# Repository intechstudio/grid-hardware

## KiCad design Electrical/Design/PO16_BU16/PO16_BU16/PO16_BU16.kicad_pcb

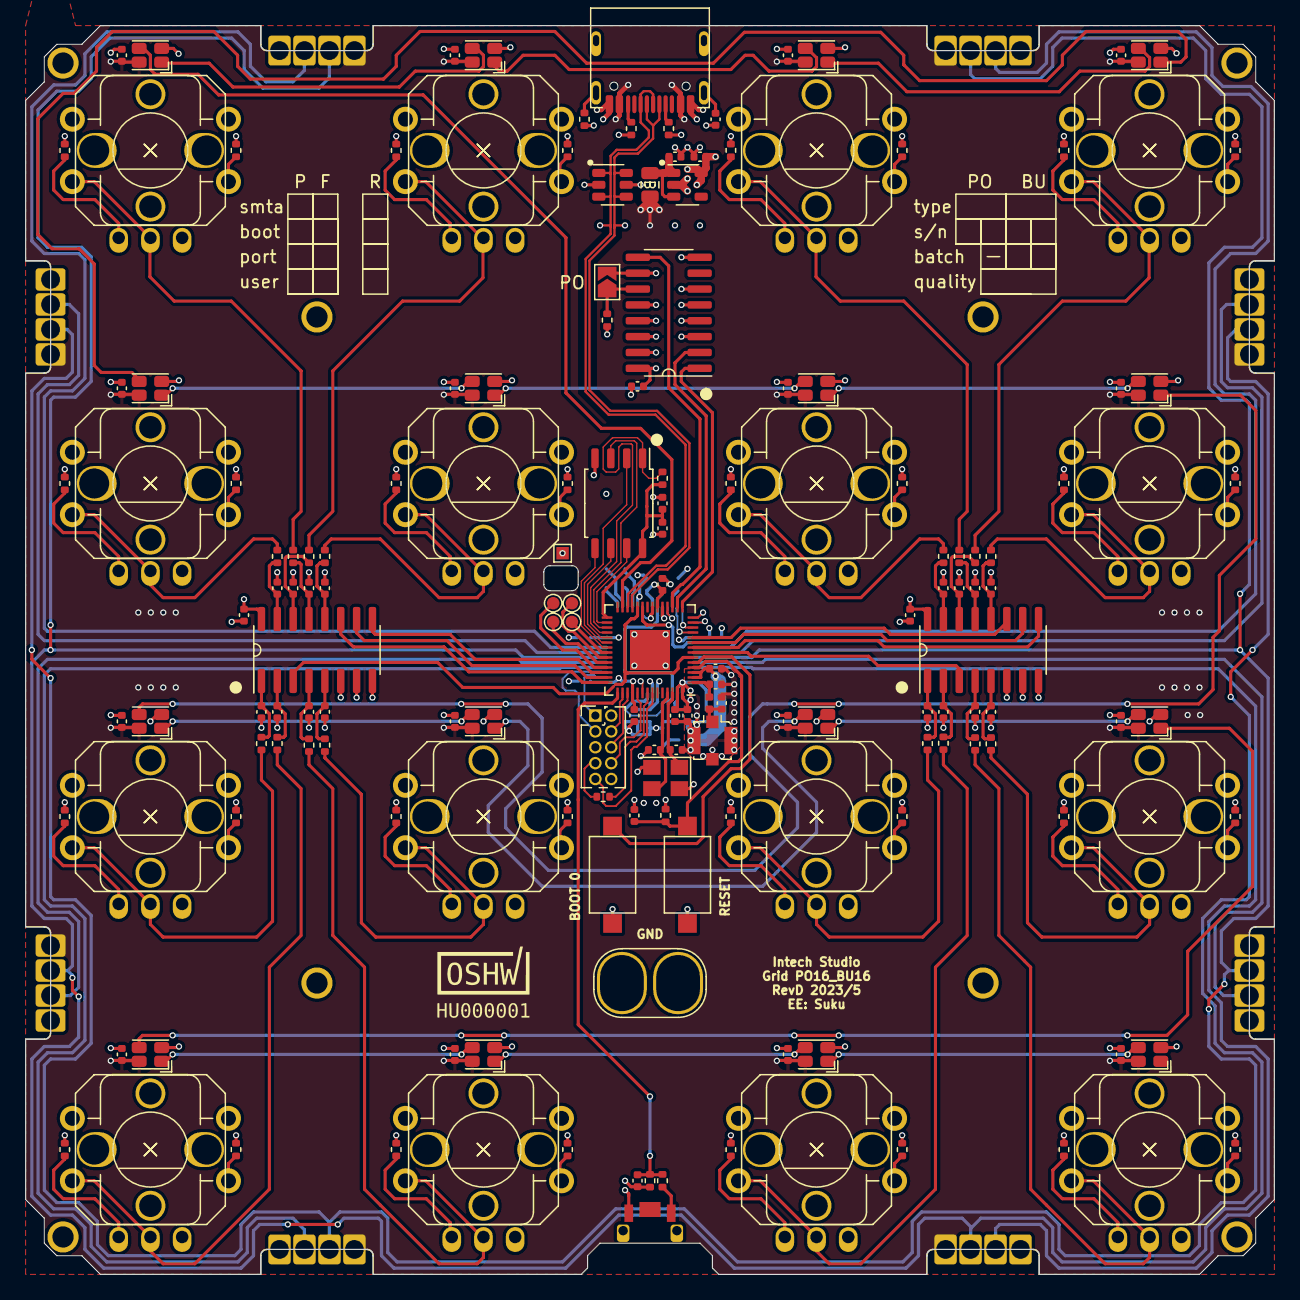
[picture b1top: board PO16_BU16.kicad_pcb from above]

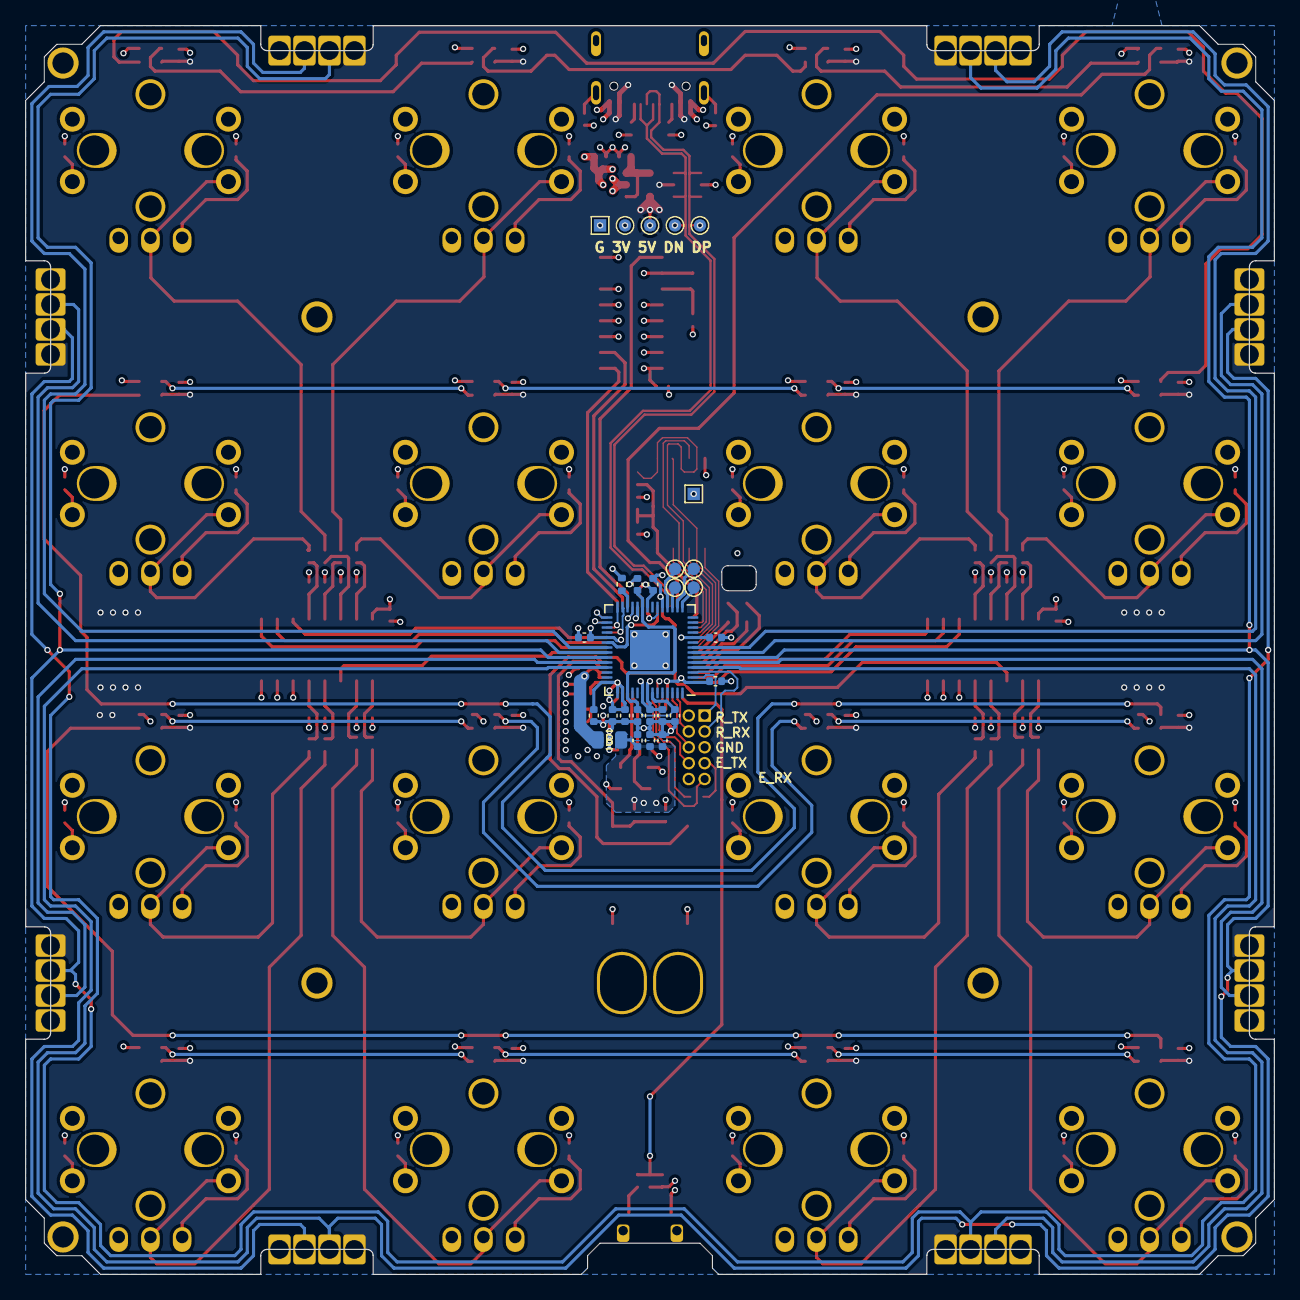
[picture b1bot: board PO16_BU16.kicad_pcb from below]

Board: 4 copper layers, 100.0 x 100.0 mm, 217 parts (28 on the bottom side), 155 nets.

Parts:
C731, C732, C735, C736, C737, C738, C740, C741, C744, C745, C747, C749, C751, C752, C756, C757, C801, C901, C902, C903, C904, C905, C906, C907, C908, C909, C910, C911, C912, C913, C914, C915, C916, C1001, C1002, C1003, C1004, C1005, C1006, C1007, C1008, C1009, C1010, C1011, C1012, C1013, C1014, C1015, C1016, C1017, C1018: 100n; CAP_0402
C733, C734, C746, C754, C755, C758, C760, C761: 1u; CAP_0402
C739: 3p9; CAP_0402
C742: 1p8; CAP_0402
C743: 10u; CAP_0402
C748, C750: 10p; CAP_0402
C753: 10n; CAP_0402
C759: 4n7; CAP_0402
D901, D902, D903, D904, D905, D906, D907, D908, D909, D910, D911, D912, D913, D914, D915, D916: WS2812C-2020; UI_WS2812C-2020
J701: Conn_Coaxial; U.FL_Molex_MCRF_73412-0110_Vertical
J702: (NF); PinHeader_2x05_P1.27mm_Vertical
J703, J704, J705, J706, J707, J708, J709, J710: AFB10-S08LCA-00; J_INTERFACE_SPRINGPATTERN
J711: USB_C_TYPE-C-32-M-12; USB_C_Korean_Hroparts_TYPE-C-31-M-12
J799: Conn_01x02; OscilloscopeGround
JP801: (NF); SolderJumper-2_P1.3mm_Open_TrianglePad1.0x1.5mm
L701: 1n8; IND_0402
L702, L703: GZ2012D601TF; FERRIT_0805
LOGO701: LOGO; OSHWA
M701: (NF); grid_outline
R701, R729, R734, R735, R738, R739, R801, R1033, R1034, R1035, R1036, R1037, R1038, R1039, R1040, R1041, R1042, R1043, R1044, R1045, R1046, R1047, R1048: 5k1; RES_0402
R733, R736, R1001, R1002, R1003, R1004, R1005, R1006, R1007, R1008, R1009, R1010, R1011, R1012, R1013, R1014, R1015, R1016: 1k; RES_0402
R737: 1M; RES_0402
R1017, R1018, R1019, R1020, R1021, R1022, R1023, R1024, R1025, R1026, R1027, R1028, R1029, R1030, R1031, R1032: 470R; RES_0402
SW701: C255807; SW_HYP_MAPMODE
SW702, SW703: C2905169; SW_SPST_CK_RS282G05A3
TP701, TP702, TP703, TP704, TP706, TP707, TP708, TP709: TestPoint; TestPoint_Pad_D1.0mm
TP705, TP710: TestPoint; TestPoint_Pad_1.0x1.0mm
TP711: GND; TestPoint_Pad_1.0x1.0mm
TP712: VB; TestPoint_Pad_D1.0mm
TP713: D-; TestPoint_Pad_D1.0mm
TP714: D+; TestPoint_Pad_D1.0mm
TP715: UI; TestPoint_Pad_D1.0mm
U703: RP2040; RP2040_QFN-56-1EP_7x7mm_P0.4mm_EP3.2x3.2mm
U704: ESP32-S3FN8; QFN-56-1EP_7x7mm_P0.4mm_EP3.2x3.2mm
U705: W25Q64JVSSIQ; SOIC-8W_FLASH
U706: SESRV05-4; SOT-23-6
U707: LN1134A332MR-G; SOT-23-5
U801: 74HC165; SOIC-16_74HC165
U1001, U1002: 74HC4051; SOIC-16_74HC4051
UI1001, UI1002, UI1003, UI1004, UI1005, UI1006, UI1007, UI1008, UI1009, UI1010, UI1011, UI1012, UI1013, UI1014, UI1015, UI1016: P090S-04F20BR10K (NF); UI_POT_TT
UI1017, UI1018, UI1019, UI1020, UI1021, UI1022, UI1023, UI1024, UI1025, UI1026, UI1027, UI1028, UI1029, UI1030, UI1031, UI1032: B3F-4050 (NF); UI_BUTTON_OMRON
Y701: ESP32_XTAL; Crystal_SMD_Abracon_ABM8G-4Pin_3.2x2.5mm

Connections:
+1V1: C731.1, C732.1, C733.1, U703.23 (DVDD), U703.45 (VREG_VOUT), U703.50 (DVDD)
+3V3: C734.1, C735.1, C736.1, C737.1, C738.1, C740.1, C741.1, C743.1, C744.1, C745.1, C746.1, C747.1, C751.1, C752.1, C753.1, C754.1, C757.2, C761.2, C801.1, C1009.1, C1018.1, L702.2, R701.1, R729.1, R735.1, R801.1, R1017.1, R1018.1, R1019.1, R1020.1, R1021.1, R1022.1, R1023.1, R1024.1, R1025.1, R1026.1, R1027.1, R1028.1, R1029.1, R1030.1, R1031.1, R1032.1, R1033.2, R1034.2, R1035.2, R1036.2, R1037.2, R1038.2, R1039.2, R1040.2, R1041.2, R1042.2, R1043.2, R1044.2, R1045.2, R1046.2, R1047.2, R1048.2, TP715.1, U703.1 (IOVDD), U703.10 (IOVDD), U703.22 (IOVDD), U703.33 (IOVDD), U703.42 (IOVDD), U703.43 (ADC_AVDD), U703.44 (VREG_IN), U703.48 (USB_VDD), U703.49 (IOVDD), U704.20 (VDD3P3_RTC), U704.46 (VDD3P3_CPU), U704.55 (VDDA1), U704.56 (VDDA2), U707.5 (OUT), U801.6 (D7), U801.16 (VCC), U1001.16 (VDD), U1002.16 (VDD)
+5V: C901.2, C902.2, C903.2, C904.2, C905.2, C906.2, C907.2, C908.2, C909.2, C910.2, C911.2, C912.2, C913.2, C914.2, C915.2, C916.2, D901.4 (VDD), D902.4 (VDD), D903.4 (VDD), D904.4 (VDD), D905.4 (VDD), D906.4 (VDD), D907.4 (VDD), D908.4 (VDD), D909.4 (VDD), D910.4 (VDD), D911.4 (VDD), D912.4 (VDD), D913.4 (VDD), D914.4 (VDD), D915.4 (VDD), D916.4 (VDD), J703.4, J704.1, J705.1, J706.4, J707.4, J708.1, J709.1, J710.4, J711.A4B9 (VBUS), J711.A9B4 (VBUS), L703.2, TP712.1, U706.5
/ANA_0: R1001.2, UI1001.2, UI1017.3
/ANA_1: R1005.2, UI1005.2, UI1021.3
/ANA_2: R1009.2, UI1009.2, UI1025.3
/ANA_3: R1013.2, UI1013.2, UI1029.3
/ANA_4: R1002.2, UI1002.2, UI1018.3
/ANA_5: R1006.2, UI1006.2, UI1022.3
/ANA_6: R1010.2, UI1010.2, UI1026.3
/ANA_7: R1014.2, UI1014.2, UI1030.3
/ANA_8: R1003.2, UI1003.2, UI1019.3
/ANA_9: R1007.2, UI1007.2, UI1023.3
/ANA_10: R1011.2, UI1011.2, UI1027.3
/ANA_11: R1015.2, UI1015.2, UI1031.3
/ANA_12: R1004.2, UI1004.2, UI1020.3
/ANA_13: R1008.2, UI1008.2, UI1024.3
/ANA_14: R1012.2, UI1012.2, UI1028.3
/ANA_15: R1016.2, UI1016.2, UI1032.3
/HWCFG/HWCFG_CLOCK: U704.16 (GPIO11), U801.2 (CLK)
/HWCFG/HWCFG_DATA: U704.17 (GPIO12), U801.9 (Q)
/HWCFG/HWCFG_SHIFT: U704.15 (GPIO10), U801.1 (SH/~LD)
/MCU/ESP_BOOT0: SW703.2 (B), U704.5 (GPIO0)
/MCU/ESP_LNA: C742.1, L701.2, U704.1 (LNA_IN)
/MCU/ESP_RESET: C758.1, R735.2, SW702.2 (B), U704.4 (CHIP_PU)
/MCU/GRID_EAST_RX: J709.3, U703.36 (GPIO24)
/MCU/GRID_EAST_TX: J710.2, U703.38 (GPIO26_ADC0)
/MCU/GRID_NORTH_RX: J705.3, U703.8 (GPIO6)
/MCU/GRID_NORTH_TX: J707.2, U703.35 (GPIO23)
/MCU/GRID_SOUTH_RX: J708.3, U703.39 (GPIO27_ADC1)
/MCU/GRID_SOUTH_TX: J706.2, U703.4 (GPIO2)
/MCU/GRID_SYNC_1: J703.3, J706.3, J707.3, J710.3, U703.37 (GPIO25)
/MCU/GRID_SYNC_2: J704.2, J705.2, J708.2, J709.2, U703.6 (GPIO4)
/MCU/GRID_WEST_RX: J704.3, U703.5 (GPIO3)
/MCU/GRID_WEST_TX: J703.2, U703.7 (GPIO5)
/MCU/LED_DATA_OUT: D901.3 (DIN), U704.27 (GPIO21)
/MCU/MAP_MODE: C757.1, R701.2, R736.2, U704.43 (GPIO38)
/MCU/RP_CLK: U703.20 (XIN), U704.21 (GPIO15)
/MCU/RP_INTERRUPT: U703.34 (GPIO22), U704.23 (GPIO17)
/MCU/RP_RUN: R729.2, U703.26 (RUN)
/MCU/RP_SPI0_CS: U703.28 (GPIO17), U704.12 (GPIO7)
/MCU/RP_SPI0_RX: U703.27 (GPIO16), U704.11 (GPIO6)
/MCU/RP_SPI0_SCK: U703.29 (GPIO18), U704.14 (GPIO9)
/MCU/RP_SPI0_TX: U703.30 (GPIO19), U704.13 (GPIO8)
/MCU/RP_SWCLK: U703.24 (SWCLK), U704.19 (GPIO14)
/MCU/RP_SWDIO: U703.25 (SWD), U704.18 (GPIO13)
/MCU/RP_UART0_RX: J702.3, U703.3 (GPIO1)
/MCU/RP_UART0_TX: J702.1, U703.2 (GPIO0)
/MCU/SPICLK: U704.33 (GPIO30), U705.6 (CLK)
/MCU/SPICS0: R734.2, U704.32 (GPIO29), U705.1 (~CS)
/MCU/SPID: U704.35 (GPIO32), U705.5 (DI(IO0))
/MCU/SPIHD: U704.30 (GPIO27), U705.7 (IO3)
/MCU/SPIQ: U704.34 (GPIO31), U705.2 (DO(IO1))
/MCU/SPIWP: U704.31 (GPIO28), U705.3 (IO2)
/MCU/TCK: J702.4, U704.44 (GPIO39)
/MCU/TDI: J702.8, U704.47 (GPIO41)
/MCU/TDO: J702.6, U704.45 (GPIO40)
/MCU/TMS: J702.2, U704.48 (GPIO42)
/MCU/U0RXD: J702.9, U704.50 (GPIO44)
/MCU/U0TXD: R733.2, U704.49 (GPIO43)
/MCU/USB_DN: J711.A7 (D-), J711.B7 (D-), TP713.1, U704.25 (GPIO19), U706.4, U706.6
/MCU/USB_DP: J711.A6 (D+), J711.B6 (D+), TP714.1, U704.26 (GPIO20), U706.1, U706.3
ESP_GPIO_1: U704.6 (GPIO1), U704.24 (GPIO18), U1001.3 (X)
ESP_GPIO_2: U704.7 (GPIO2), U1002.3 (X)
ESP_GPIO_3: U704.8 (GPIO3), U1002.9 (C)
ESP_GPIO_4: U704.9 (GPIO4), U1002.10 (B)
ESP_GPIO_5: U704.10 (GPIO5), U1002.11 (A)
ESP_GPIO_33: TP709.1, U704.38 (GPIO33)
ESP_GPIO_34: TP708.1, U704.39 (GPIO34)
ESP_GPIO_35: U704.40 (GPIO35), U1001.9 (C)
ESP_GPIO_36: U704.41 (GPIO36), U1001.10 (B)
ESP_GPIO_37: U704.42 (GPIO37), U1001.11 (A)
ESP_GPIO_47: TP706.1, U704.37 (GPIO47)
ESP_GPIO_48: TP707.1, U704.36 (GPIO48)
GND: C731.2, C732.2, C733.2, C734.2, C735.2, C736.2, C737.2, C738.2, C739.2, C740.2, C741.2, C742.2, C743.2, C744.2, C745.2, C746.2, C747.2, C748.2, C749.2, C750.2, C751.2, C752.2, C753.2, C754.2, C755.2, C756.2, C758.2, C759.2, C760.2, C761.1, C801.2, C901.1, C902.1, C903.1, C904.1, C905.1, C906.1, C907.1, C908.1, C909.1, C910.1, C911.1, C912.1, C913.1, C914.1, C915.1, C916.1, C1001.2, C1002.2, C1003.2, C1004.2, C1005.2, C1006.2, C1007.2, C1008.2, C1009.2, C1010.2, C1011.2, C1012.2, C1013.2, C1014.2, C1015.2, C1016.2, C1017.2, C1018.2, D901.2 (VSS), D902.2 (VSS), D903.2 (VSS), D904.2 (VSS), D905.2 (VSS), D906.2 (VSS), D907.2 (VSS), D908.2 (VSS), D909.2 (VSS), D910.2 (VSS), D911.2 (VSS), D912.2 (VSS), D913.2 (VSS), D914.2 (VSS), D915.2 (VSS), D916.2 (VSS), J701.2 (Ext), J702.5, J703.1, J704.4, J705.4, J706.1, J707.1, J708.4, J709.4, J710.1, J711.A1B12 (GND), J711.A12B1 (GND), J799.1, J799.2, JP801.2 (B), R737.2, R738.2, R739.2, SW701.2 (B), SW702.1 (A), SW703.1 (A), TP705.1, TP710.1, TP711.1, U703.19 (TESTEN), U703.57 (GND), U704.57 (GND), U705.4 (GND), U706.2, U707.2 (GND), U801.3 (D4), U801.4 (D5), U801.5 (D6), U801.8 (GND), U801.10 (SI), U801.12 (D1), U801.13 (D2), U801.14 (D3), U801.15 (INH), U1001.6 (Inh), U1001.7 (VEE), U1001.8 (VSS), U1002.6 (Inh), U1002.7 (VEE), U1002.8 (VSS), UI1001.3, UI1002.3, UI1003.3, UI1004.3, UI1005.3, UI1006.3, UI1007.3, UI1008.3, UI1009.3, UI1010.3, UI1011.3, UI1012.3, UI1013.3, UI1014.3, UI1015.3, UI1016.3, UI1017.1, UI1017.2, UI1018.1, UI1018.2, UI1019.1, UI1019.2, UI1020.1, UI1020.2, UI1021.1, UI1021.2, UI1022.1, UI1022.2, UI1023.1, UI1023.2, UI1024.1, UI1024.2, UI1025.1, UI1025.2, UI1026.1, UI1026.2, UI1027.1, UI1027.2, UI1028.1, UI1028.2, UI1029.1, UI1029.2, UI1030.1, UI1030.2, UI1031.1, UI1031.2, UI1032.1, UI1032.2, Y701.2, Y701.4
unnamed: C749.1, L702.1, U704.2 (VDD3P3), U704.3 (VDD3P3)
unnamed: C760.1, L703.1, U707.1 (IN), U707.3 (EN)
unnamed: C759.1, J711.S1 (SHIELD)
unnamed: D901.1 (DOUT), D905.3 (DIN)
unnamed: D902.3 (DIN), D913.1 (DOUT)
unnamed: D902.1 (DOUT), D906.3 (DIN)
unnamed: D903.3 (DIN), D914.1 (DOUT)
unnamed: D903.1 (DOUT), D907.3 (DIN)
unnamed: D904.3 (DIN), D915.1 (DOUT)
unnamed: D904.1 (DOUT), D908.3 (DIN)
unnamed: D905.1 (DOUT), D909.3 (DIN)
unnamed: D906.1 (DOUT), D910.3 (DIN)
unnamed: D907.1 (DOUT), D911.3 (DIN)
unnamed: D908.1 (DOUT), D912.3 (DIN)
unnamed: D909.1 (DOUT), D913.3 (DIN)
unnamed: D910.1 (DOUT), D914.3 (DIN)
unnamed: D911.1 (DOUT), D915.3 (DIN)
unnamed: D912.1 (DOUT), D916.3 (DIN)
unnamed: C739.1, J701.1 (In), L701.1
unnamed: J702.7, R733.1
unnamed: J711.A5 (CC1), R738.1
unnamed: J711.B5 (CC2), R739.1
unnamed: J711.S2 (SHIELD), R737.1
unnamed: JP801.1 (A), R801.2, U801.11 (D0)
unnamed: R1017.2, UI1001.1
unnamed: R1018.2, UI1002.1
unnamed: R1019.2, UI1003.1
unnamed: R1020.2, UI1004.1
unnamed: R1021.2, UI1005.1
unnamed: R1022.2, UI1006.1
unnamed: R1023.2, UI1007.1
unnamed: R1024.2, UI1008.1
unnamed: R1025.2, UI1009.1
unnamed: R1026.2, UI1010.1
unnamed: R1027.2, UI1011.1
unnamed: R1028.2, UI1012.1
unnamed: R1029.2, UI1013.1
unnamed: R1030.2, UI1014.1
unnamed: R1031.2, UI1015.1
unnamed: R1032.2, UI1016.1
unnamed: R1033.1, UI1017.4
unnamed: R1034.1, UI1018.4
unnamed: R1035.1, UI1019.4
unnamed: R1036.1, UI1020.4
unnamed: R1037.1, UI1021.4
unnamed: R1038.1, UI1022.4
unnamed: R1039.1, UI1023.4
unnamed: R1040.1, UI1024.4
unnamed: R1041.1, UI1025.4
unnamed: R1042.1, UI1026.4
unnamed: R1043.1, UI1027.4
unnamed: R1044.1, UI1028.4
unnamed: R1045.1, UI1029.4
unnamed: R1046.1, UI1030.4
unnamed: R1047.1, UI1031.4
unnamed: R1048.1, UI1032.4
unnamed: R736.1, SW701.1 (A)
unnamed: TP701.1, U703.15 (GPIO12)
unnamed: TP702.1, U703.16 (GPIO13)
unnamed: TP703.1, U703.17 (GPIO14)
unnamed: TP704.1, U703.18 (GPIO15)
unnamed: C750.1, U704.53 (XTAL_N), Y701.3
unnamed: C748.1, U704.54 (XTAL_P), Y701.1
unnamed: C1001.1, R1001.1, U1001.13 (X0)
unnamed: C1005.1, R1005.1, U1001.14 (X1)
unnamed: C1002.1, R1002.1, U1001.15 (X2)
unnamed: C1006.1, R1006.1, U1001.12 (X3)
unnamed: C1003.1, R1003.1, U1001.1 (X4)
unnamed: C1007.1, R1007.1, U1001.5 (X5)
unnamed: C1004.1, R1004.1, U1001.2 (X6)
unnamed: C1008.1, R1008.1, U1001.4 (X7)
unnamed: C1010.1, R1009.1, U1002.13 (X0)
unnamed: C1014.1, R1013.1, U1002.14 (X1)
unnamed: C1011.1, R1010.1, U1002.15 (X2)
unnamed: C1015.1, R1014.1, U1002.12 (X3)
unnamed: C1012.1, R1011.1, U1002.1 (X4)
unnamed: C1016.1, R1015.1, U1002.5 (X5)
unnamed: C1013.1, R1012.1, U1002.2 (X6)
unnamed: C1017.1, R1016.1, U1002.4 (X7)
VDD_SPI: C755.1, C756.1, R734.1, U704.29 (VDD_SPI), U705.8 (VCC)

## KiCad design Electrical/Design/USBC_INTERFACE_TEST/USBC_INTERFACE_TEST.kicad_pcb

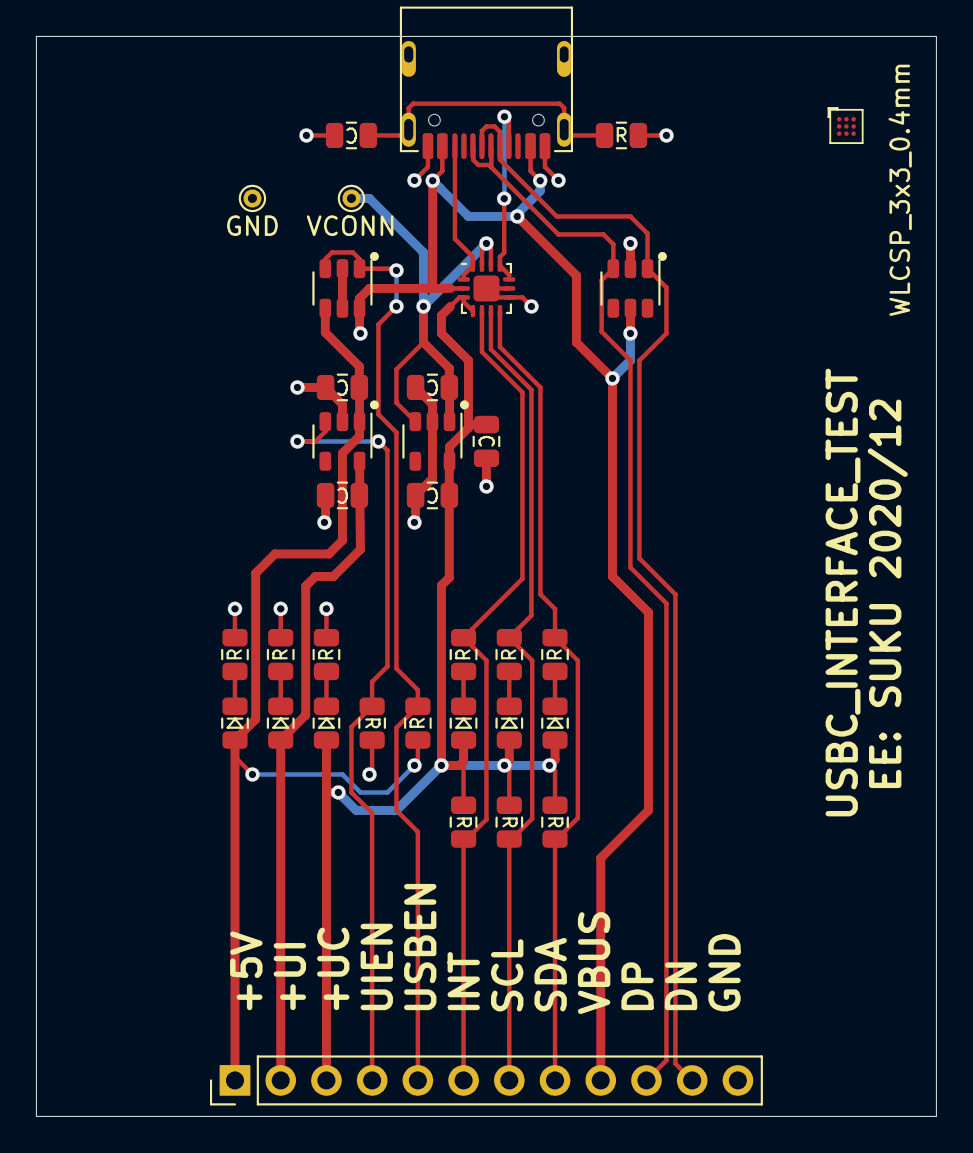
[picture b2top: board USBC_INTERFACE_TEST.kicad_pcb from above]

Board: 2 copper layers, 50.0 x 60.0 mm, 33 parts (0 on the bottom side), 23 nets.

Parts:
C1: 100n; CAP_0805
C2, C3, C4, C5: 1u; CAP_0805
C6: 4n7; CAP_0805
D1, D2, D3, D4, D5, D6: LED; LED_0805
J1: USB_C_TYPE-C-32-M-12; USB_C_Korean_Hroparts_TYPE-C-31-M-12
J2: Conn_01x12; PinHeader_1x12_P2.54mm_Vertical
Q1: WST2011; SOT-23-6
R1: 1M; RES_0805
R2, R4, R5: 2k2; RES_0805
R3, R6, R12: 10k; RES_0805
R7, R8, R9, R10, R11: 5k1; RES_0805
TP1: GND; TestPoint_THTPad_D1.0mm_Drill0.5mm
TP2: VCONN; TestPoint_THTPad_D1.0mm_Drill0.5mm
U1: FUSB302BMPX; WQFN-14-1EP_2.5x2.5mm_P0.5mm_EP1.45x1.45mm
U2, U3: U_REGULATOR_SOT23-5; SOT-23-5
U4: U_ESD_4ch; SOT-23-6

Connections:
+3V3_UC: C1.1, C2.1, D3.2, D4.2, D5.2, D6.2, J2.3, R2.1, R4.1, R5.1, U1.3, U1.4, U3.5
+3V3_UI: C5.1, D2.2, J2.2, U2.5
+5V: C3.1, D1.2, J2.1, Q1.4, R12.1, U2.1
/CC1: J1.A5, U1.10, U1.11
/CC2: J1.B5, U1.1, U1.14
/UI_PWR_EN: J2.4, R3.1, U2.3
/USB_DN: J1.A7, J1.B7, J2.11, U4.1
/USB_DP: J1.A6, J1.B6, J2.10, U4.3
/USB_INT: J2.6, R5.2, R9.2, U1.5
/USB_PWR_EN: J2.5, Q1.1, Q1.3, R12.2
/USB_SCL: J2.7, R4.2, R10.2, U1.6
/USB_SDA: J2.8, R2.2, R11.2, U1.7
/VCONN: C4.1, TP2.1, U1.12, U1.13, U3.1, U3.3
GND: C1.2, C2.2, C3.2, C4.2, C5.2, C6.2, J1.A1B12, J1.A12B1, J2.12, R1.2, R3.2, R6.2, R7.2, R8.2, TP1.1, U1.8, U1.9, U1.15, U2.2, U3.2, U4.2
unnamed: C6.1, J1.S1, J1.S2, R1.1
unnamed: D1.1, R6.1
unnamed: D2.1, R7.1
unnamed: D3.1, R8.1
unnamed: D4.1, R9.1
unnamed: D5.1, R10.1
unnamed: D6.1, R11.1
unnamed: Q1.2, Q1.5
VBUS: J1.A4B9, J1.A9B4, J2.9, Q1.6, U1.2, U4.5

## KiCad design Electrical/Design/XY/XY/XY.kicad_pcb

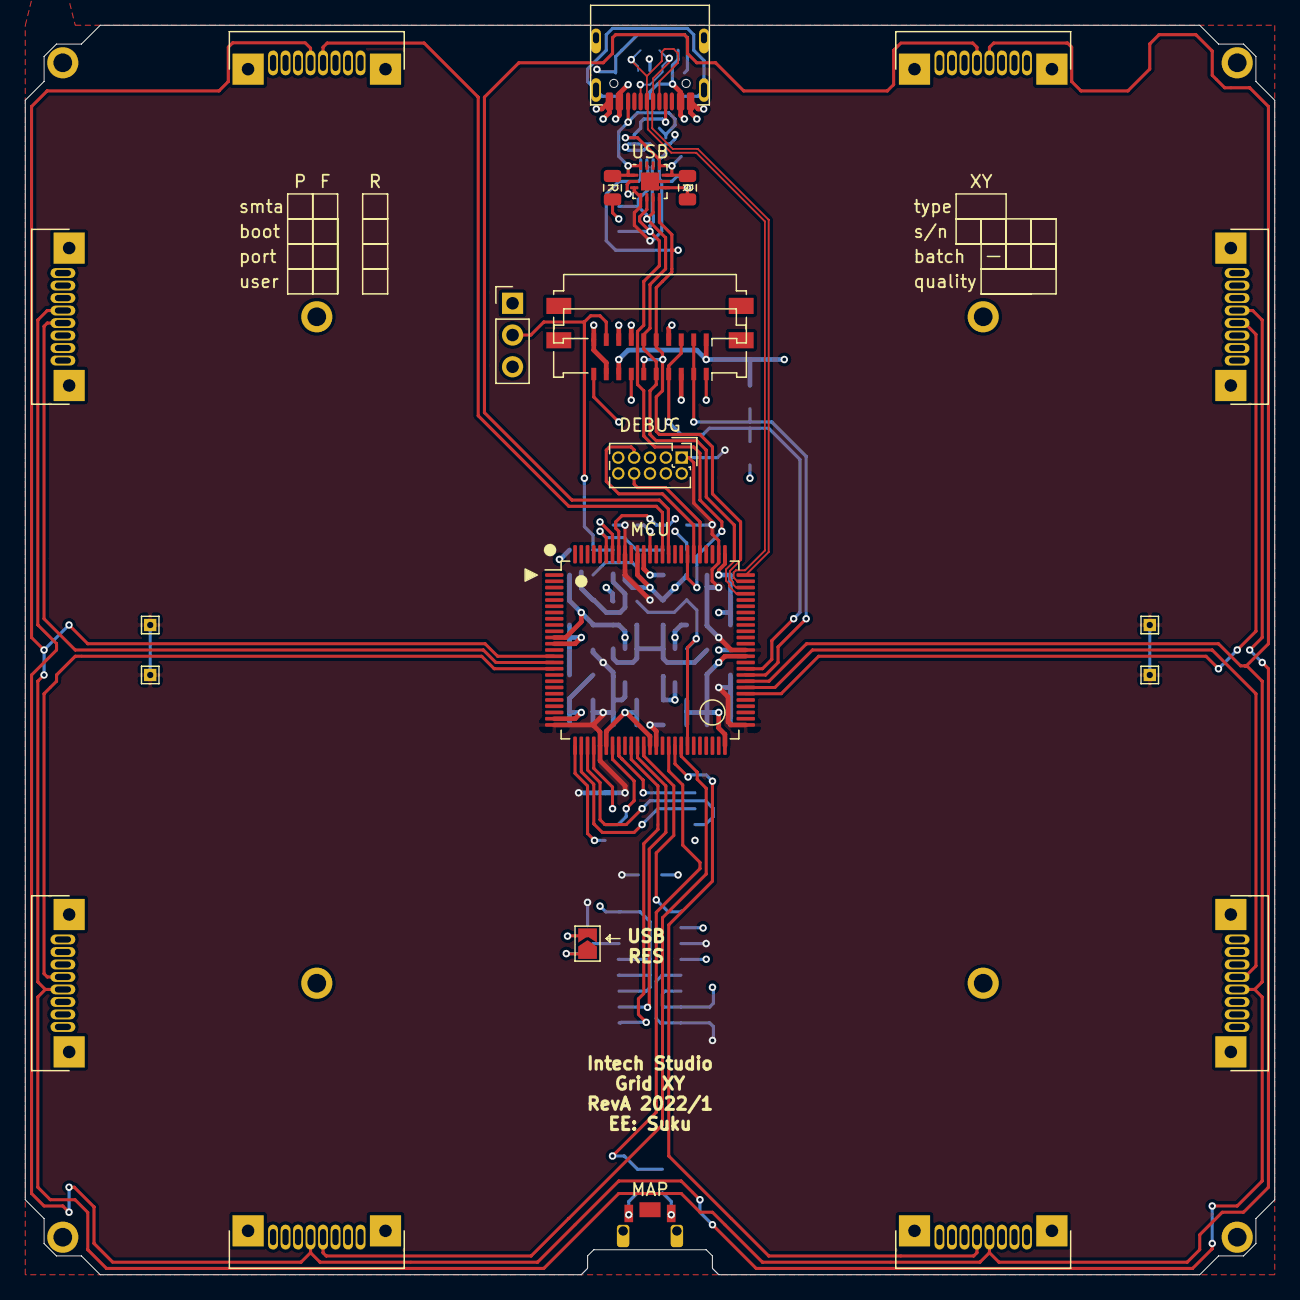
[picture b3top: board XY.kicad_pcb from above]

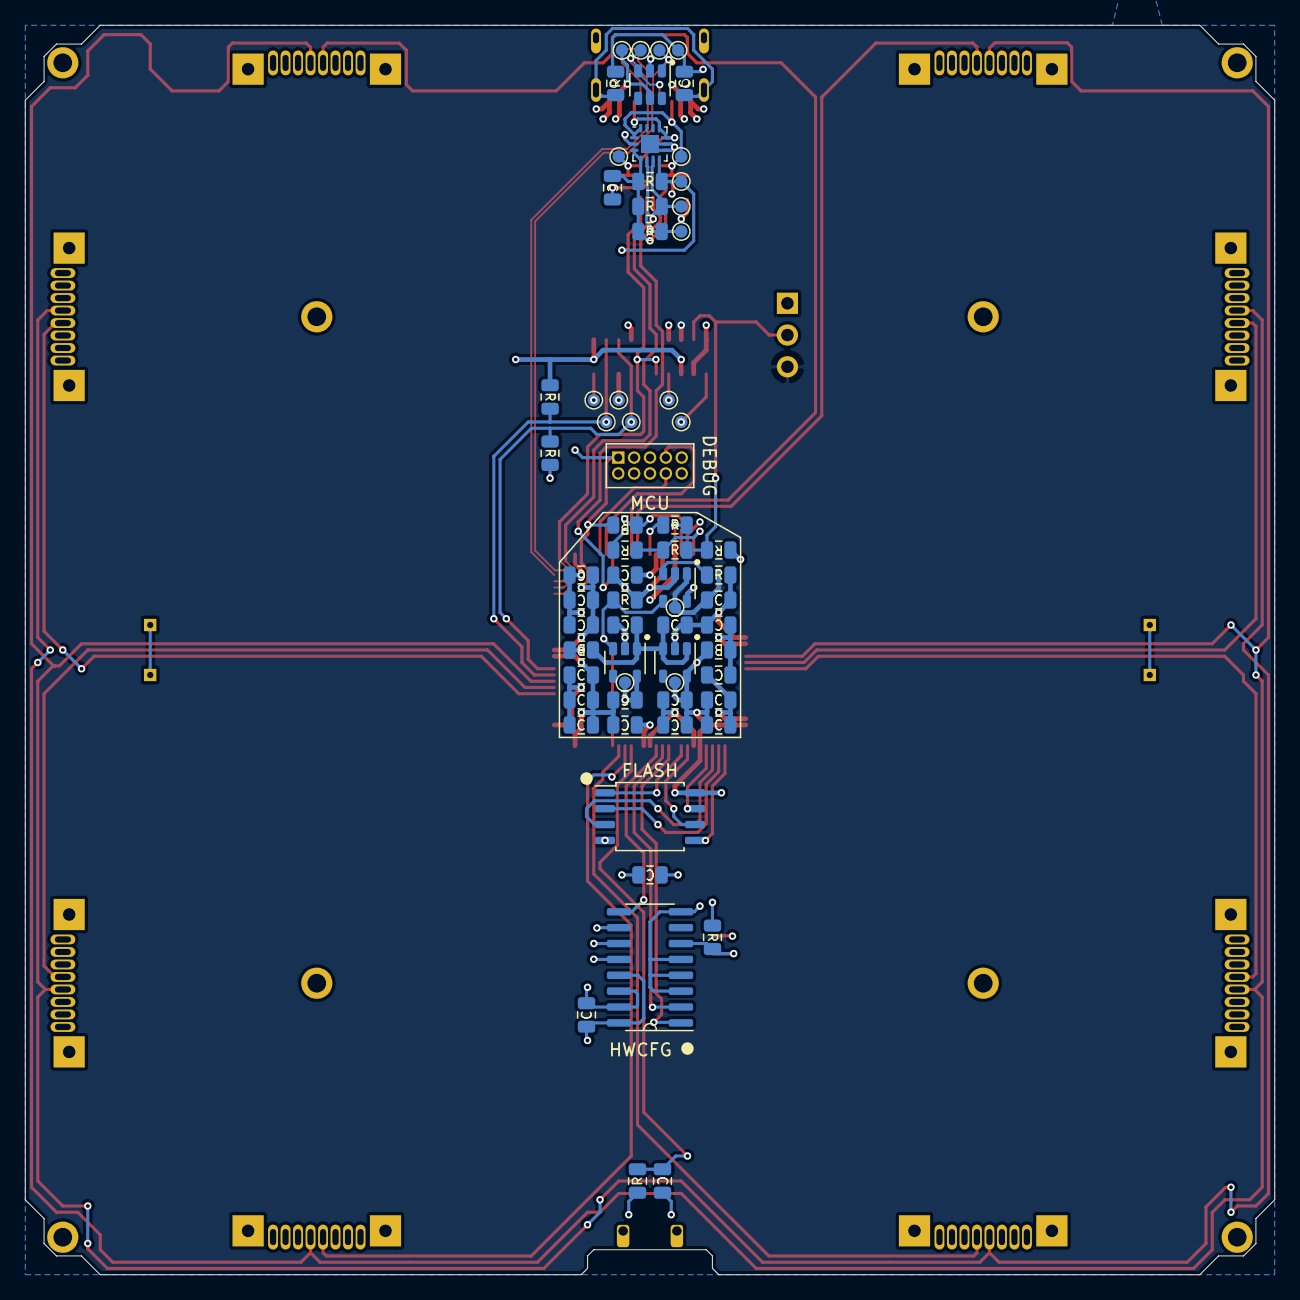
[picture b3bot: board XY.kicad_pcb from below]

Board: 4 copper layers, 100.0 x 100.0 mm, 89 parts (65 on the bottom side), 53 nets.

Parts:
C33, C39, C41, C42, C44, C45, C46, C47, C48, C49, C51, C54, C55, C94, C95: 100n; CAP_0805
C34, C36, C40, C50, C53: 1u; CAP_0805
C37: 4n7; CAP_0805
C38, C43: 10u; CAP_0805
J1: USB_C_TYPE-C-32-M-12; USB_C_Korean_Hroparts_TYPE-C-31-M-12
J2: (NF); PinHeader_2x05_P1.27mm_Vertical
J3: (NF); PinHeader_1x03_P2.54mm_Vertical
J4, J5, J6, J7, J8, J9, J10, J11: C20110 (NF); grid_ffc_8_vertical
J12: C262716; Molex_200528-0100_1x10-1MP_P1.00mm_Horizontal
J13: C262716 (NF); Molex_200528-0100_1x10-1MP_P1.00mm_Horizontal
JP2: (NF); SolderJumper-2_P1.3mm_Open_TrianglePad1.0x1.5mm
L1, L2: GZ2012D601TF; FERRIT_0805
M1: (NF); grid_outline
R1, R2, R36, R111, R112: 10k; RES_0805
R34, R37, R107, R108, R109, R110: 5k1; RES_0805
R35: 1M; RES_0805
R38, R39, R40, R41, R42: 1k; RES_0805
SW1: C255807; SW_HYP_MAPMODE
TP1, TP2, TP3, TP4: TestPoint; TestPoint_THTPad_1.0x1.0mm_Drill0.5mm
TP5: D-; TestPoint_Pad_D1.0mm
TP6: D+; TestPoint_Pad_D1.0mm
TP7: GND; TestPoint_Pad_D1.0mm
TP8: VB; TestPoint_Pad_D1.0mm
TP9: UC; TestPoint_Pad_D1.0mm
TP10: UI; TestPoint_Pad_D1.0mm
TP11: UI_5V; TestPoint_Pad_D1.0mm
TP12: MXT_DSS; TestPoint_Pad_D1.0mm
TP13: MXT_DDATA; TestPoint_Pad_D1.0mm
TP14: MXT_DCLK; TestPoint_Pad_D1.0mm
TP15: MXT_INT; TestPoint_Pad_D1.0mm
TP16: SDA; TestPoint_Pad_D1.0mm
TP17: SCL; TestPoint_Pad_D1.0mm
TP18: INT; TestPoint_Pad_D1.0mm
TP19: CC1; TestPoint_Pad_D1.0mm
TP20: CC2; TestPoint_Pad_D1.0mm
TP21: MXT_RST; TestPoint_Pad_D1.0mm
TP22: MXT_GND; TestPoint_Pad_D1.0mm
U3: 74HC165; SOIC-16_74HC165
U4: SESRV05-4; SOT-23-6
U5, U6: LN1134A332MR-G; SOT-23-5
U7: SAMD51N20A; TQFP-100_14x14mm_P0.5mm
U8: W25Q16JVSSIQ; SOIC-8W_FLASH
U15, U16: FUSB302BMPX (NF); WQFN-14-1EP_2.5x2.5mm_P0.5mm_EP1.45x1.45mm
U17: MT9700; SOT-23-5

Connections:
+3V3_UC: C33.1, C40.1, C41.1, C42.1, C43.1, C44.1, C45.1, C46.1, C47.1, C48.1, C51.1, C54.1, C55.1, C94.1, J2.1, L1.2, R38.2, R39.2, R108.1, R109.1, R110.1, R112.1, TP1.1, TP2.1, TP3.1, TP4.1, TP9.1, U3.11, U3.13, U3.16, U5.5, U7.25, U7.30, U7.39, U7.51, U7.63, U7.77, U7.92, U8.8, U15.3, U15.4, U16.3, U16.4
+3V3_UI: C36.1, J12.8, J13.1, R1.1, TP10.1, U6.5
+5V: J1.A4B9, J1.A9B4, J4.1, J4.2, J4.3, J5.6, J5.7, J5.8, J6.6, J6.7, J6.8, J7.1, J7.2, J7.3, J8.1, J8.2, J8.3, J9.6, J9.7, J9.8, J10.6, J10.7, J10.8, J11.1, J11.2, J11.3, L2.2, R34.1, TP8.1, U4.5, U15.2, U16.2, U17.5
+5V_UI: C50.1, J3.3, J13.8, TP11.1, U17.1
/HWCFG/HWCFG_CLOCK: U3.2, U7.36
/HWCFG/HWCFG_DATA: U3.9, U7.37
/HWCFG/HWCFG_SHIFT: U3.1, U7.35
/MCU/GRID_AUX_RX: J2.8, U7.80
/MCU/GRID_AUX_TX: J2.7, U7.81
/MCU/GRID_EAST_RX: J7.4, U7.56
/MCU/GRID_EAST_TX: J9.5, U7.57
/MCU/GRID_NORTH_RX: J4.4, U7.86
/MCU/GRID_NORTH_TX: J5.5, U7.85
/MCU/GRID_SOUTH_RX: J11.4, U7.42
/MCU/GRID_SOUTH_TX: J10.5, U7.43
/MCU/GRID_SYNC_1: J5.4, J6.4, J9.4, J10.4, U7.58
/MCU/GRID_SYNC_2: J4.5, J7.5, J8.5, J11.5, U7.14
/MCU/GRID_WEST_RX: J8.4, U7.16
/MCU/GRID_WEST_TX: J6.5, U7.15
/MCU/MAP_MODE: C95.1, R40.2, U7.41
/MCU/MUX_ADDRESS_A: J12.2, J13.2, R1.2, TP15.1, U7.59
/MCU/MUX_ADDRESS_B: J12.4, J13.3, R2.1, TP21.1, U7.60
/MCU/QSPI_IO_0: U7.26, U8.5
/MCU/QSPI_IO_1: U7.27, U8.2
/MCU/QSPI_IO_2: U7.28, U8.3
/MCU/QSPI_IO_3: U7.29, U8.7
/MCU/QSPI_SCK: U7.32, U8.6
/MCU/QSPI_~CE: U7.33, U8.1
/MCU/SYS_I2C_INT_0: R110.2, TP18.1, U7.82, U15.5, U16.5
/MCU/SYS_RESET: J2.10, R38.1, U7.88
/MCU/SYS_SWCLK: J2.4, R39.1, U7.93
/MCU/SYS_SWDIO: J2.2, U7.94
/MCU/SYS_SWO: J2.6, R41.2
/MCU/Sheet60FB6C45/USB_CC1: J1.A5, R37.1, TP19.1, U15.10, U15.11, U16.10, U16.11
/MCU/Sheet60FB6C45/USB_CC2: J1.B5, R107.1, TP20.1, U15.1, U15.14, U16.1, U16.14
/MCU/UI_PWR_EN: R36.1, U6.3, U7.44, U17.4
/MCU/USB_DN: J1.A7, J1.B7, TP5.1, U4.1, U7.74
/MCU/USB_DP: J1.A6, J1.B6, TP6.1, U4.3, U7.75
/UI_LED/DBG_CLK: J12.7, TP14.1
/UI_LED/DBG_DATA: J12.10, TP13.1
/UI_LED/DBG_SS: J12.1, TP12.1
/UI_LED/LED_DATA_IN: J3.2, J13.9, R34.2, R42.2
/UI_LED/MXT_SCL: J12.5, J13.6, R109.2, TP17.1, U7.72, U15.6, U16.6
/UI_LED/MXT_SDA: J12.6, J13.5, R108.2, TP16.1, U7.73, U15.7, U16.7
GND: C33.2, C34.2, C36.2, C37.2, C38.2, C39.2, C40.2, C41.2, C42.2, C43.2, C44.2, C45.2, C46.2, C47.2, C48.2, C49.2, C50.2, C51.2, C53.2, C54.2, C55.2, C94.2, C95.2, J1.A1B12, J1.A12B1, J2.3, J2.5, J2.9, J3.1, J4.6, J4.7, J4.8, J5.1, J5.2, J5.3, J6.1, J6.2, J6.3, J7.6, J7.7, J7.8, J8.6, J8.7, J8.8, J9.1, J9.2, J9.3, J10.1, J10.2, J10.3, J11.6, J11.7, J11.8, J12.3, J12.9, J13.4, J13.7, J13.10, JP2.2, R2.2, R35.2, R36.2, R37.2, R107.2, R111.2, SW1.2, TP7.1, TP22.1, U3.3, U3.4, U3.5, U3.8, U3.10, U3.12, U3.14, U3.15, U4.2, U5.2, U6.2, U7.11, U7.24, U7.31, U7.38, U7.50, U7.62, U7.76, U7.90, U8.4, U15.8, U15.9, U15.15, U16.8, U16.9, U16.15, U17.2
unnamed: C34.1, C53.1, L2.1, U5.1, U5.3, U6.1
unnamed: C37.1, J1.S1, J1.S2, R35.1
unnamed: C38.1, C39.1, L1.1, U7.12
unnamed: C49.1, U7.89
unnamed: JP2.1, R112.2, U3.6
unnamed: R40.1, SW1.1
unnamed: R41.1, R42.1, U7.95
unnamed: R111.1, U17.3

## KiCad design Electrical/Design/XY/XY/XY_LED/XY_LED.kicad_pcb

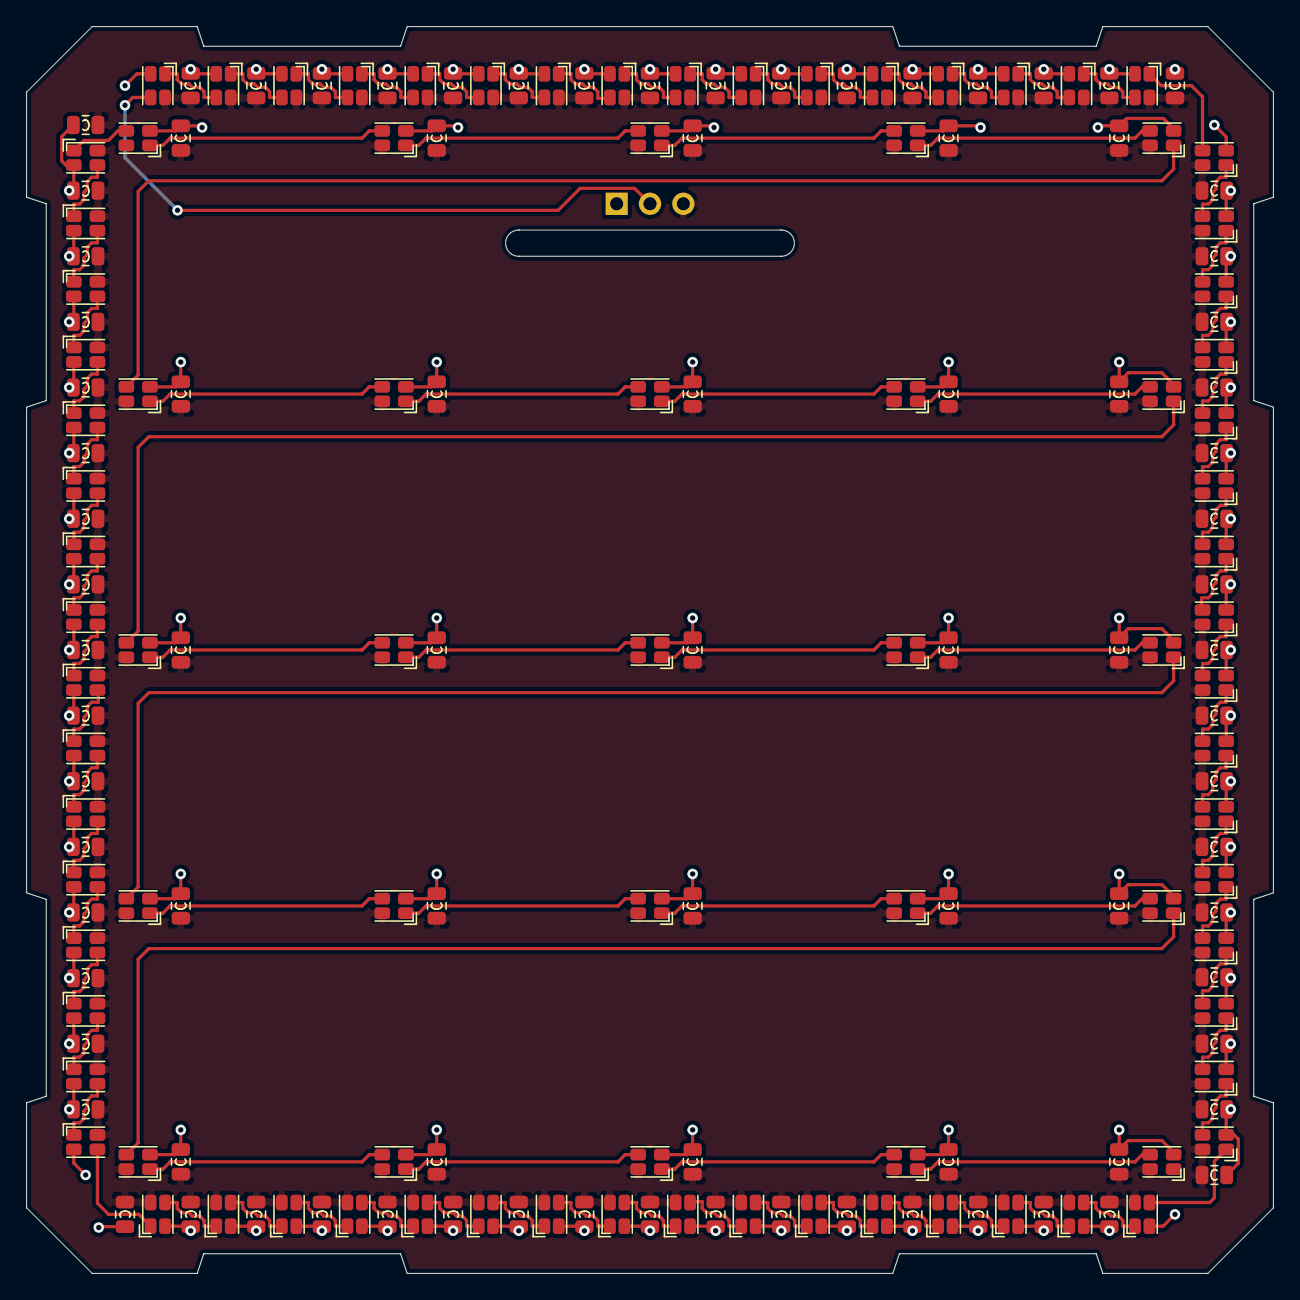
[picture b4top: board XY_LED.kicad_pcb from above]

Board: 2 copper layers, 95.0 x 95.0 mm, 179 parts (1 on the bottom side), 91 nets.

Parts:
C1, C2, C3, C4, C5, C6, C7, C8, C9, C10, C11, C12, C13, C14, C15, C16, C17, C18, C19, C20, C21, C22, C23, C24, C25, C26, C27, C28, C29, C30, C31, C32, C33, C34, C35, C36, C37, C38, C39, C40, C41, C42, C43, C44, C45, C46, C47, C48, C49, C50, C51, C52, C53, C54, C55, C56, C57, C58, C59, C60, C61, C62, C63, C64, C65, C66, C67, C68, C69, C70, C71, C72, C73, C74, C75, C76, C77, C78, C79, C80, C81, C82, C83, C84, C85, C86, C87, C88, C89: 100n; CAP_0805
D1, D2, D3, D4, D5, D6, D7, D8, D9, D10, D11, D12, D13, D14, D15, D16, D17, D18, D19, D20, D21, D22, D23, D24, D25, D26, D27, D28, D29, D30, D31, D32, D33, D34, D35, D36, D37, D38, D39, D40, D41, D42, D43, D44, D45, D46, D47, D48, D49, D50, D51, D52, D53, D54, D55, D56, D57, D58, D59, D60, D61, D62, D63, D64, D65, D66, D67, D68, D69, D70, D71, D72, D73, D74, D75, D76, D77, D78, D79, D80, D81, D82, D83, D84, D85, D86, D87, D88, D89: UI_WS2812C-2020
J1: Conn_01x03; PinHeader_1x03_P2.54mm_Vertical

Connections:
+5V: C1.1, C2.1, C3.1, C4.1, C5.1, C6.1, C7.1, C8.1, C9.1, C10.1, C11.1, C12.1, C13.1, C14.1, C15.1, C16.1, C17.1, C18.1, C19.1, C20.1, C21.1, C22.1, C23.1, C24.1, C25.1, C26.1, C27.1, C28.1, C29.1, C30.1, C31.1, C32.1, C33.1, C34.1, C35.1, C36.1, C37.1, C38.1, C39.1, C40.1, C41.1, C42.1, C43.1, C44.1, C45.1, C46.1, C47.1, C48.1, C49.1, C50.1, C51.1, C52.1, C53.1, C54.1, C55.1, C56.1, C57.1, C58.1, C59.1, C60.1, C61.1, C62.1, C63.1, C64.1, C65.1, C66.1, C67.1, C68.1, C69.1, C70.1, C71.1, C72.1, C73.1, C74.1, C75.1, C76.1, C77.1, C78.1, C79.1, C80.1, C81.1, C82.1, C83.1, C84.1, C85.1, C86.1, C87.1, C88.1, C89.1, D1.4, D2.4, D3.4, D4.4, D5.4, D6.4, D7.4, D8.4, D9.4, D10.4, D11.4, D12.4, D13.4, D14.4, D15.4, D16.4, D17.4, D18.4, D19.4, D20.4, D21.4, D22.4, D23.4, D24.4, D25.4, D26.4, D27.4, D28.4, D29.4, D30.4, D31.4, D32.4, D33.4, D34.4, D35.4, D36.4, D37.4, D38.4, D39.4, D40.4, D41.4, D42.4, D43.4, D44.4, D45.4, D46.4, D47.4, D48.4, D49.4, D50.4, D51.4, D52.4, D53.4, D54.4, D55.4, D56.4, D57.4, D58.4, D59.4, D60.4, D61.4, D62.4, D63.4, D64.4, D65.4, D66.4, D67.4, D68.4, D69.4, D70.4, D71.4, D72.4, D73.4, D74.4, D75.4, D76.4, D77.4, D78.4, D79.4, D80.4, D81.4, D82.4, D83.4, D84.4, D85.4, D86.4, D87.4, D88.4, D89.4, J1.3
/LED_DATA: D1.3, J1.2
/Sheet6050EF7D/DIN: D64.1, D65.3
/sheet5F25C68C/DIN: D32.1, D33.3
/sheet5F25EC60/DIN: D48.1, D49.3
/sheet5F211848/DIN: D16.1, D17.3
GND: C1.2, C2.2, C3.2, C4.2, C5.2, C6.2, C7.2, C8.2, C9.2, C10.2, C11.2, C12.2, C13.2, C14.2, C15.2, C16.2, C17.2, C18.2, C19.2, C20.2, C21.2, C22.2, C23.2, C24.2, C25.2, C26.2, C27.2, C28.2, C29.2, C30.2, C31.2, C32.2, C33.2, C34.2, C35.2, C36.2, C37.2, C38.2, C39.2, C40.2, C41.2, C42.2, C43.2, C44.2, C45.2, C46.2, C47.2, C48.2, C49.2, C50.2, C51.2, C52.2, C53.2, C54.2, C55.2, C56.2, C57.2, C58.2, C59.2, C60.2, C61.2, C62.2, C63.2, C64.2, C65.2, C66.2, C67.2, C68.2, C69.2, C70.2, C71.2, C72.2, C73.2, C74.2, C75.2, C76.2, C77.2, C78.2, C79.2, C80.2, C81.2, C82.2, C83.2, C84.2, C85.2, C86.2, C87.2, C88.2, C89.2, D1.2, D2.2, D3.2, D4.2, D5.2, D6.2, D7.2, D8.2, D9.2, D10.2, D11.2, D12.2, D13.2, D14.2, D15.2, D16.2, D17.2, D18.2, D19.2, D20.2, D21.2, D22.2, D23.2, D24.2, D25.2, D26.2, D27.2, D28.2, D29.2, D30.2, D31.2, D32.2, D33.2, D34.2, D35.2, D36.2, D37.2, D38.2, D39.2, D40.2, D41.2, D42.2, D43.2, D44.2, D45.2, D46.2, D47.2, D48.2, D49.2, D50.2, D51.2, D52.2, D53.2, D54.2, D55.2, D56.2, D57.2, D58.2, D59.2, D60.2, D61.2, D62.2, D63.2, D64.2, D65.2, D66.2, D67.2, D68.2, D69.2, D70.2, D71.2, D72.2, D73.2, D74.2, D75.2, D76.2, D77.2, D78.2, D79.2, D80.2, D81.2, D82.2, D83.2, D84.2, D85.2, D86.2, D87.2, D88.2, D89.2, J1.1
unnamed: D1.1, D2.3
unnamed: D2.1, D3.3
unnamed: D3.1, D4.3
unnamed: D4.1, D5.3
unnamed: D5.1, D6.3
unnamed: D6.1, D7.3
unnamed: D7.1, D8.3
unnamed: D8.1, D9.3
unnamed: D10.1, D11.3
unnamed: D9.1, D10.3
unnamed: D11.1, D12.3
unnamed: D12.1, D13.3
unnamed: D13.1, D14.3
unnamed: D14.1, D15.3
unnamed: D15.1, D16.3
unnamed: D17.1, D18.3
unnamed: D18.1, D19.3
unnamed: D19.1, D20.3
unnamed: D20.1, D21.3
unnamed: D21.1, D22.3
unnamed: D22.1, D23.3
unnamed: D23.1, D24.3
unnamed: D24.1, D25.3
unnamed: D25.1, D26.3
unnamed: D26.1, D27.3
unnamed: D27.1, D28.3
unnamed: D28.1, D29.3
unnamed: D29.1, D30.3
unnamed: D30.1, D31.3
unnamed: D31.1, D32.3
unnamed: D33.1, D34.3
unnamed: D34.1, D35.3
unnamed: D35.1, D36.3
unnamed: D36.1, D37.3
unnamed: D37.1, D38.3
unnamed: D38.1, D39.3
unnamed: D39.1, D40.3
unnamed: D40.1, D41.3
unnamed: D41.1, D42.3
unnamed: D42.1, D43.3
unnamed: D43.1, D44.3
unnamed: D44.1, D45.3
unnamed: D45.1, D46.3
unnamed: D46.1, D47.3
unnamed: D47.1, D48.3
unnamed: D49.1, D50.3
unnamed: D50.1, D51.3
unnamed: D51.1, D52.3
unnamed: D52.1, D53.3
unnamed: D53.1, D54.3
unnamed: D54.1, D55.3
unnamed: D55.1, D56.3
unnamed: D56.1, D57.3
unnamed: D57.1, D58.3
unnamed: D58.1, D59.3
unnamed: D59.1, D60.3
unnamed: D60.1, D61.3
unnamed: D61.1, D62.3
unnamed: D62.1, D63.3
unnamed: D63.1, D64.3
unnamed: D65.1, D66.3
unnamed: D66.1, D67.3
unnamed: D67.1, D68.3
unnamed: D68.1, D69.3
unnamed: D69.1, D70.3
unnamed: D70.1, D71.3
unnamed: D71.1, D72.3
unnamed: D72.1, D73.3
unnamed: D73.1, D74.3
unnamed: D74.1, D75.3
unnamed: D75.1, D76.3
unnamed: D76.1, D77.3
unnamed: D77.1, D78.3
unnamed: D78.1, D79.3
unnamed: D79.1, D80.3
unnamed: D80.1, D81.3
unnamed: D81.1, D82.3
unnamed: D82.1, D83.3
unnamed: D83.1, D84.3
unnamed: D84.1, D85.3
unnamed: D85.1, D86.3
unnamed: D86.1, D87.3
unnamed: D87.1, D88.3
unnamed: D88.1, D89.3
